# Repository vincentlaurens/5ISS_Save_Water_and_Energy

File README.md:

# Sensibilisation tool to save water and energy

Written by ILYA team

# Table of Contents
1. [Introduction](#introduction)
2. [TreeMap of the repository](#paragraph1)
3. [Architecture of the solution](#paragraph2)
4. [Device Layer](#paragraph3)
5. [Network Layer](#paragraph4)
6. [Application Layer](#paragraph5)
7. [VM](#paragraph7)
8. [Deployment](#paragraph8)

## Introduction 

Nowadays, people are becoming increasingly concerned about the future of our planet. The consequences of climate change are worse every year. Fighting against it has become a source of inspiration for many young entrepreneurs. ILYA is a young startup that is developing two products: a cyclic shower to reduce water consumption and an awareness tool to sensitive people to save water, energy and therefore money when taking a shower. In this report, we present in detail the second product, a tool that allows measuring in real-time the water and energy consumption during a shower. The prototype we developed consists of a sensor system that collects data on the water flow and quantity, stores it in a database, and then display an analysis of this data on a web interface.  The data is captured by an autonomous and energy-efficient node and is then sent via WiFi to a local server to be stored in a database and then on the cloud. The final prototype is not fully optimized but both simple and realistic.

## TreeMap of the repository 
```
Project ILYA
    |-README
    |-Documentation
    |   |-rapport.pdf
    |   |-Presentation.pdf
    |-DeviceLayer
    |   |-ESP_Code
    |-ApplicationLayer
    |   |-data_structure_api
    |   |-UI
    |-VM
    |   |-README
```

## Architecture of the solution 

## Device Layer 

The Device layer is Composed of 4 different components for one module.
There are 2 sensors , 1 Microcontroller, 1 Shield.
This is the Bom of our Module:

|DEVICE NAME	                       |Quantity |
| -----------------------------------: | ------: |
|Grove - Temperature Sensor V1.2       |    x1   |
|YFS-201 Hall Effect Water Flow Sensor |    x1   |
|Node-MCU ESP8266	X1                 |    x1   |
|Grove Base Shield for NodeMCU         |    x1   |

The Arduino Code can retrieve data from sensors during a certain period : each 10 sec
Number of acquisition : 7 , Total time of acquisition : 70 sec.

This parameters are configurable in the source code which is commented to know the purposes of functions and variables
<a href="https://drive.google.com/file/d/1UWVMobrCpHeJf4AdiO7gw0xYP0oA8SGS/view?usp=sharing">Bill of Material (document)</a>

## Network Layer 

1.  Create an account on http://maqiatto.com
   Click on "CREATE ACCOUNT"
   Create your account
2.  After login, clic on your email address on the left top corner
   On the dropdown menu clic on "Broker configuration"
3.  Next page should appear
    
    ADD the same topics as shown on the figure (cf First part :Device Layer where you have to replace created topic on the  global code variables)
4. Once differents topics are created you can monitor reception of JSON object by connecting to the http://www.hivemq.com/demos/websocket-client/ on a private window in your browser.
    Then you have to fill all the fields as shown in the next figure
    
    Note that vlaurens@etud.insa-toulouse.fr/ilya is the main topic where all data are going to be sent. ( <maqiattoUsername>/ilya ingeneral).
 Ajouter image après  connexion

## Application Layer 

You can deploy the application either on a Ubuntu Virtual Machine or by deploying containers as describe in part 7 or on your computer if you have python installed but you will need to install some python modules using command and install mongo (https://docs.mongodb.com/manual/installation/) and for configuring data base mongodb-compass (https://www.mongodb.com/products/compass)
````
$  sudo apt-get update && apt-get install -y apt-utils && apt-get install -y python && apt-get install -y python-pip && pip install requests && pip install flask && pip install flask_restplus && pip install paho-mqtt && pip install pymongo
````
Then if you decide to install on your machine you have to install npm and nodejs (https://nodejs.org/fr/download/) to be able to install node-red and run the UI.

Then you will download the "ApplicationLayer/data_structure_api" folder from git repository

Move on the folder and run command:
````
$ python app.py
````

The API is ready to collect data from broker and store it on mongodb.

Then run 
````
$ node-red
````
Then open a browser and go on http://127.0.0.1:1880

If you can't show flows import the two flows which are on folder "ApplictionLayer/UI" as described on the following tutorial: https://nodered.org/docs/user-guide/editor/workspace/import-export.

  If some package are missing install "node-red-contrib-ui" via install menu of nodered.
  
    - Go on the same menu as import 
    - Choose "manage Palette"
    - Go on install package section
    - Search "node-red-contrib-ui" and install it
    - Exit and close "manage Palette" popup
    - Then Deploy Flow by clicking on "Deploy" Button.
    - Visit http://127.0.0.1:1880/ui
    
Then we present you a means to install a VM or the VM we prepare and do the same operation to deploy application on the VM.

We finally show how to deploy our application with containers docker instead of using VM. A better solution for a large scale deployment.

Notice : The VM can be deploy directly on a cloud platform.

## VM 
- Download the VM on the link : https://drive.google.com/drive/folders/14bD5Wj_I1dPEdrXSYJpSs-G7y7vcGLyr?usp=sharing
- Install VirtualBox and launch the VM. You can do like in this tutorial :<a href="https://www.vulgarisation-informatique.com/installer-virtualbox.php"> How to install VirtualBox and launch VM</a>
- Connect to the VM using  ilya/ilya then you have a document which explains every thing on the VM Desktop.
- Go on API folder
```bash 
  $ cd ~/Documents/API/data_structure_api/
  ```
 - Run the API like describe on Application Layer section:
 ````
$ python app.py
````
- Open a browser and enter http://127.0.0.1:1880/ui to show dashboards.
- If you can't access it:
- Run on a Terminal (ctrl+Alt+T) : node-red  command
 ```bash 
  $ node-red
  ```
- Then go on http://127.0.0.1:1880 you will see code of flows and then you can modify them or deploy them.
  You will find flows on 
  ```bash 
  $ cd ~/Documents/API/UI/
  ```
  If you can't show them import the two flows which are on folder "ApplictionLayer/UI" as described on the following tutorial: https://nodered.org/docs/user-guide/editor/workspace/import-export.
  If some package are missing install "node-red-contrib-ui" via install menu of nodered.
  
    - Go on the same menu as import 
    - Choose "manage Palette"
    - Go on install package section
    - Search "node-red-contrib-ui" and install it
    - Exit and close "manage Palette" popup
    - Then Deploy Flow by clicking on "Deploy" Button.
    - Visit http://127.0.0.1:1880/ui
  
  If you want to monitor DataBase you can open a terminal (you can use shortcut ctrl+Alt+T) enter the command : "mongodb-compass&"
  
- Then open a browser and see the interface. enter 127.0.0.1:27017 and press enter.
  You will see all the databases. The databases are created by the API at the first data reception.
  
  <a src="./VM/README.md">VM Documentation</a>
  
## How to deploy our services on cloud by barely method or using a host OS 

In folder "services" run following command to deploy services
```bash
$ docker-compose up -d
```
run following command to stop all services
```bash
$ docker-compose down
```

Then open 127.0.0.1:1880 and on the interface
select menu on the top-right corner
In the menu select "manage palette" and in install menu
Install node-red-dashboards

Then select import menu and import two json file which are located in folder ilyaUI directory

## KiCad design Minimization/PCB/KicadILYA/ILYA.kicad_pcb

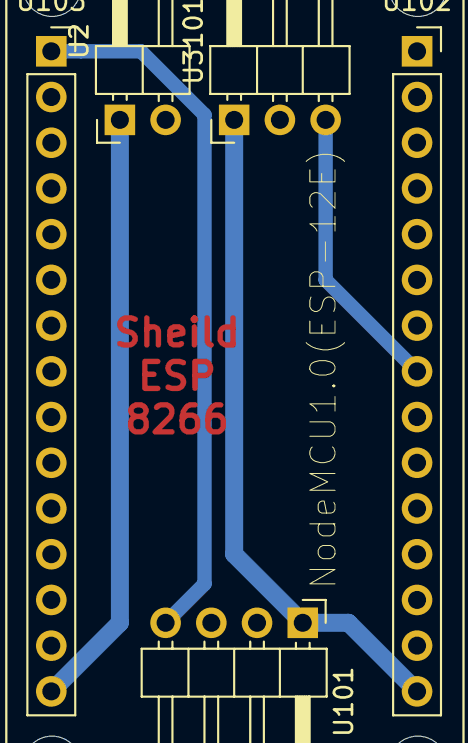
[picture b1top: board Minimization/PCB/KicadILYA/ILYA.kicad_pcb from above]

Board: 2 copper layers, 6 parts (0 on the bottom side), 5 nets.

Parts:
U1: NodeMCU1.0(ESP-12E); SEEED_113990105_withoutPin
U2: Relay_2_pins; PinHeader_1x02_P2.54mm_Horizontal
U101: Temperature_connector; PinHeader_1x04_P2.54mm_Horizontal
U102: Pin-SocketESP8266_1x15_2; PinSocket_1x15_P2.54mm_Vertical2
U103: Pin-SocketESP8266_1x15; PinSocket_1x15_P2.54mm_Vertical
U3101: Flow_connector; PinHeader_1x03_P2.54mm_Horizontal

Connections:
+3V3: U101.1, U102.16, U3101.1
+5V: U2.1, U103.15
GND: U2.2, U101.2, U103.14, U3101.2
SIGFlow: U102.23, U3101.3
SIGtemp: U101.4, U103.1

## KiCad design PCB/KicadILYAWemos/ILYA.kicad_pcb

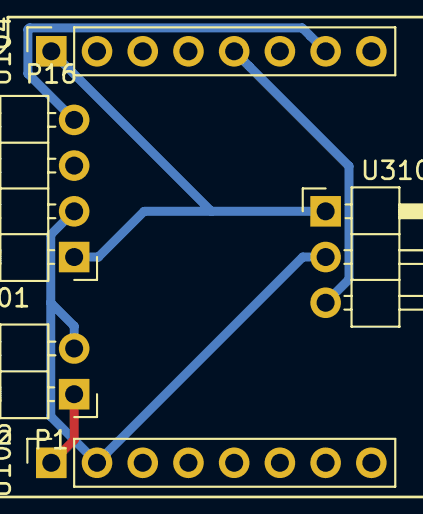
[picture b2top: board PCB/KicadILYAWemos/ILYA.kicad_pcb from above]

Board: 2 copper layers, 6 parts (0 on the bottom side), 5 nets.

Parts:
U2: Relay_2_pins; PinHeader_1x02_P2.54mm_Horizontal
U101: Temperature_connector; PinHeader_1x04_P2.54mm_Horizontal
U102: WeMos_mini; wemos-d1-mini-withoutpin
U103: Pin_socket_1x8; PinSocket_1x08_P2.54mm_Vertical
U104: Pin-socket2_1x08; PinSocket_1x08_P2.54mm_Vertical2
U3101: Flow_connector; PinHeader_1x03_P2.54mm_Horizontal

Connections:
+5V: U2.1, U103.1
GND: U2.2, U101.2, U103.2, U3101.2
SIGFlow: U104.12, U3101.3
SIGTemp: U101.4, U104.10
VCC: U101.1, U104.16, U3101.1

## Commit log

2019-11-08 Create README.md
    Draft version
2019-11-19 add ESP32 communication with broker mqtt
2019-11-20 Dashboards for demo with mqtt broker
2019-11-20 Node-Red MongoDB with dashbaords
    Stiil to check data parsing before printing on dashboards
2019-11-21 [Ilya]: dashboards real-time
2019-11-21 [Ilya]: dashboards from mongoDB
2019-11-21 [Ilya] : to check how to iterate table
2019-11-21 [Ilya] : remote mongoDB
2019-11-29 VM Conf
2019-11-29 VM/Conf without mongoDB
2019-11-30 onem2m
2019-11-30 docker nodered
2019-11-30 Mongo install VM
2019-12-01 [VM]: How to start the packaged VM
2019-12-01 nodered container
2019-12-01 Create Dockerfile-mongo
2019-12-01 refactor
2019-12-01 Update Dockerfile
2019-12-01 adding esp8266 mqtt+tempDeb
2019-12-19 PCB NODEMCU + PCB WEMOS
2019-12-19 Adding wifiMan
2019-12-19 Routage Bon mais connexion pins?
2019-12-19 PCB Wemos
2019-12-20 Wemos routage bon mais pin socket error pad near to pad
2019-12-20 Wemos pcb good
2019-12-20 Sheild esp8266 good
2019-12-21 Seild Wemos good
2019-12-28 Video Kicad
2020-01-06 New routage dimensions
2020-01-06 Correction of tracks size
2020-01-12 docker services
2020-01-12 some picture
2020-01-13 Adding fusion, mqtt publish do not work
2020-01-15 add TestFusionEEprom ok with stack datas + wifimanager id
2020-01-15 Adding ShowerDetection working
2020-01-16 ModularCode To test
2020-01-16 Code To test with card
2020-01-17 LastVersion
2020-01-19 Data API code
2020-01-21 ADD python modules installation
2020-01-21 container to test
2020-01-21 container work
2020-01-21 containers perfects
2020-01-21 mongo service update
    add port for mongo
2020-01-21 Add new node-red interface
2020-01-21 New API
2020-01-21 working for POC
2020-01-21 Manufacturing
2020-01-22 new interface
2020-01-27 added some code description
2020-01-27 REORGANIZATION
2020-01-27 Documemntation
2020-01-27 VM README
2020-01-28 hivemq
2020-01-31 added description for device layer
